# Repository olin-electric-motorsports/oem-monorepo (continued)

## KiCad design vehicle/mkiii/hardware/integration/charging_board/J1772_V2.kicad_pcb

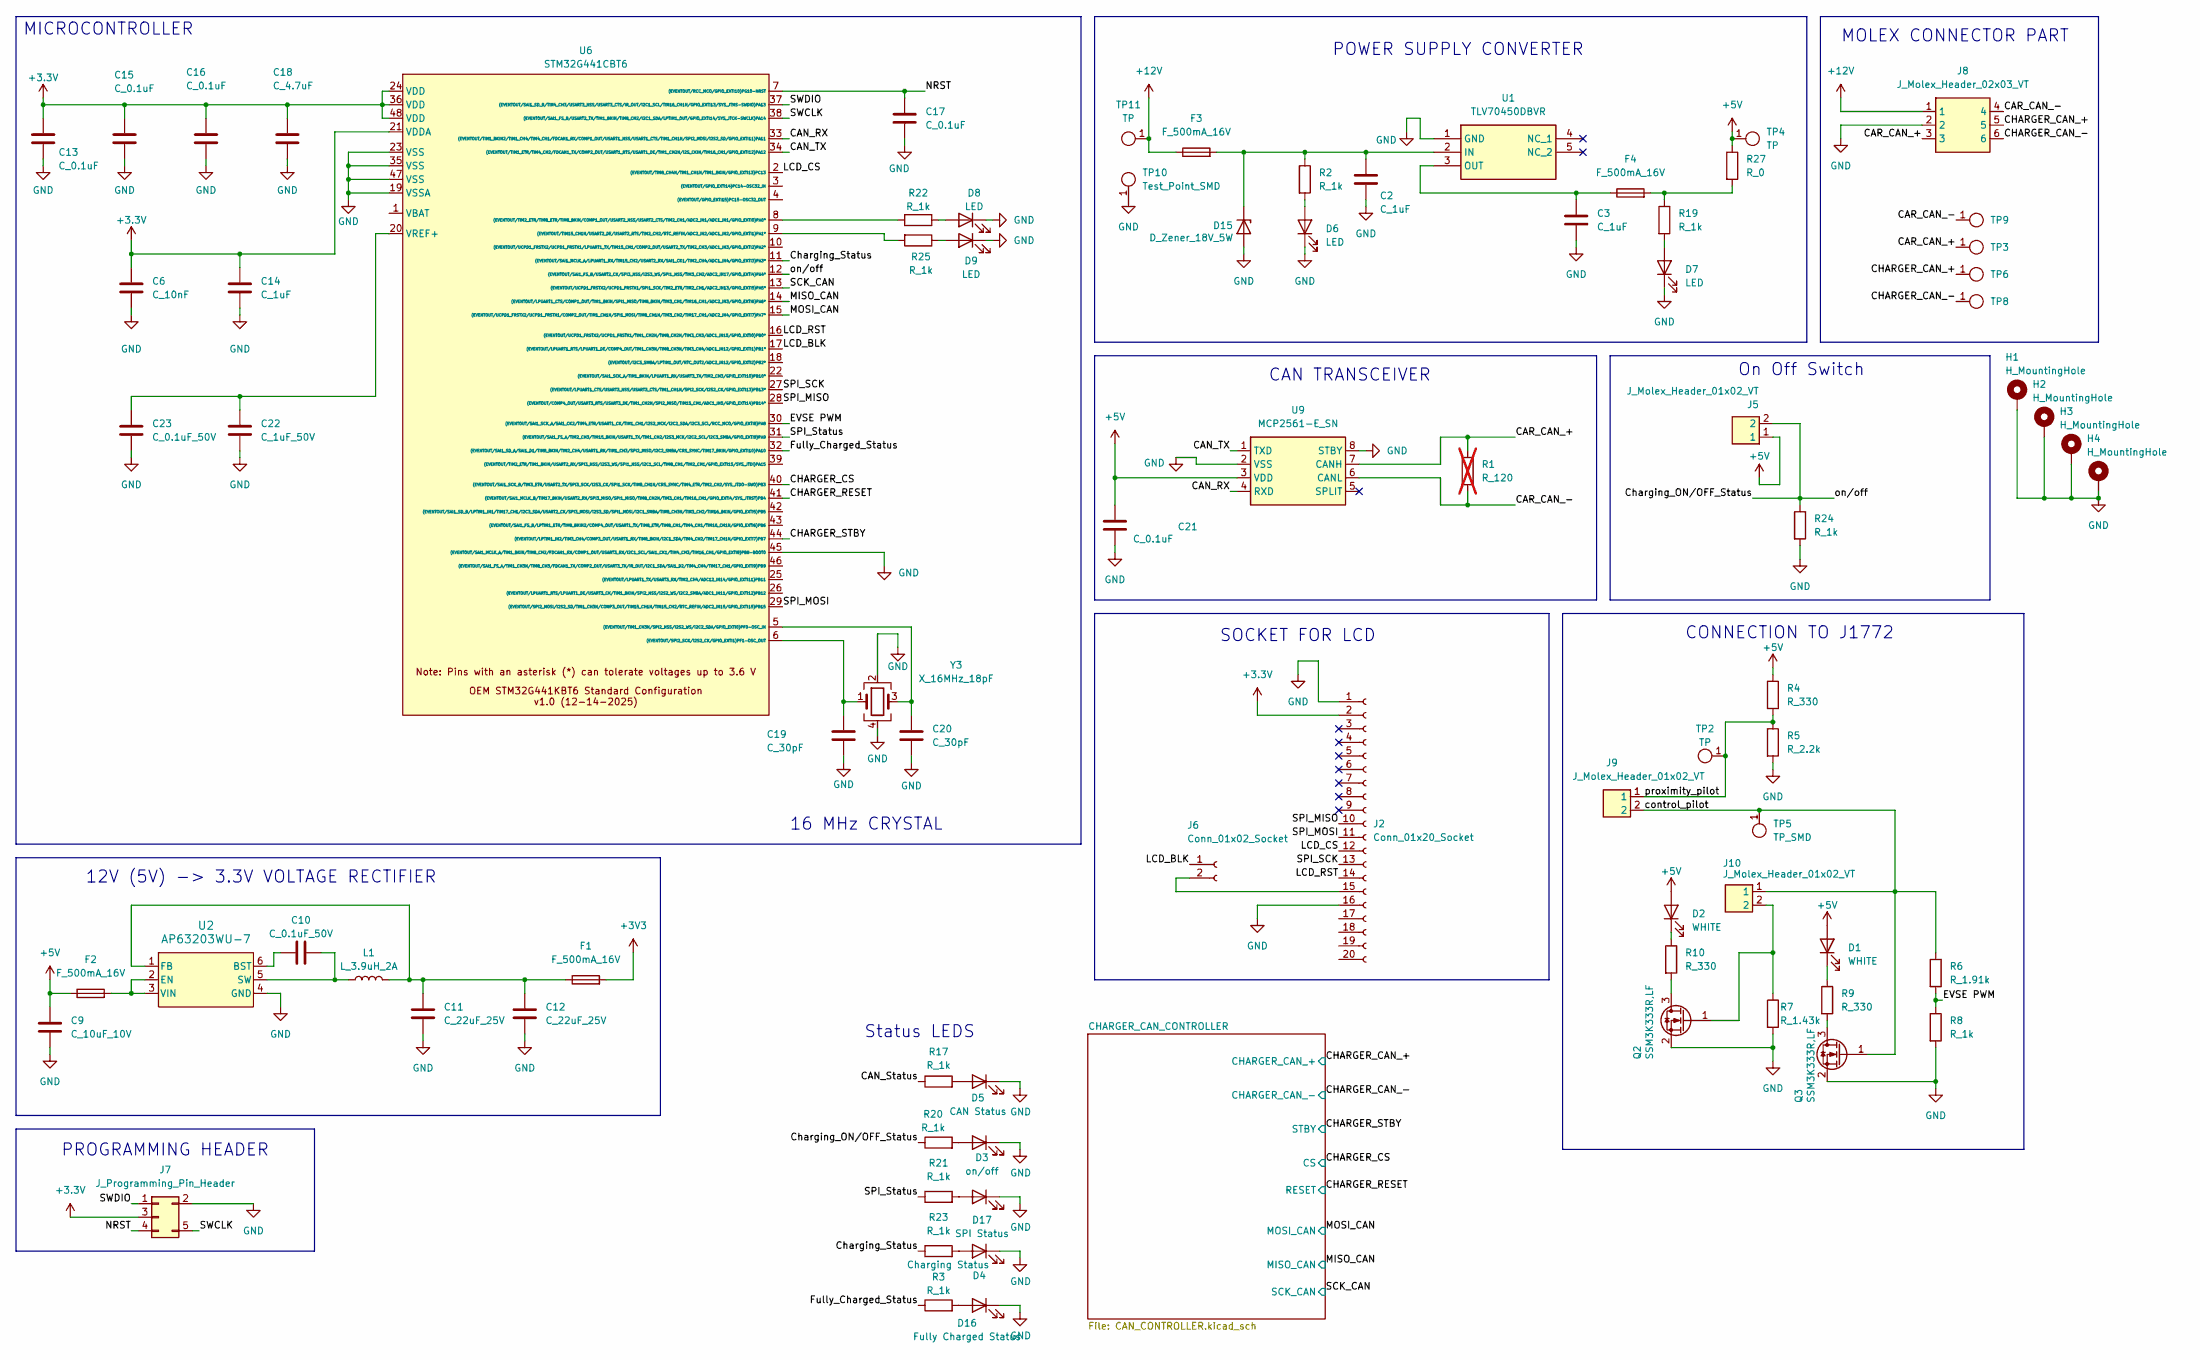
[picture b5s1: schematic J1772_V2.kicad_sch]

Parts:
C2, C14: C_1uF; C_0603_1608Metric; MPN UMK107BJ105KA-T
C3: C_1uF; C_0603_1608Metric; MPN CL10B105KA8NNNC
C6: C_10nF; C_0603_1608Metric; MPN CL10B103KB8NNNC
C9: C_10uF_10V; C_0603_1608Metric; MPN GRM188D71A106KA73D
C10, C23: C_0.1uF_50V; C_0603_1608Metric; MPN CL10B104KB8NNWC
C11, C12: C_22uF_25V; C_1206_3216Metric; MPN CL31A226KAHNNNE
C13, C15, C16, C17, C21: C_0.1uF; C_0603_1608Metric; MPN CL10B104KB8NNWC
C18: C_4.7uF; C_0603_1608Metric; MPN GRT188R61E475ME13D
C19, C20: C_30pF; C_0603_1608Metric; MPN CML0603C0G300JT50V
C22: C_1uF_50V; C_0603_1608Metric; MPN UMK107BJ105KA-T
D1, D2: WHITE; D_0805_2012Metric; MPN QBLP631-IW
D3: on/off; D_0805_2012Metric; MPN LTST-C171KRKT
D4: Charging Status; D_0805_2012Metric; MPN LTST-C171AKT
D5: CAN Status; D_0805_2012Metric; MPN LTST-C171TBKT
D6, D7, D8, D9: LED; D_0805_2012Metric; MPN QBLP631-IW
D15: D_Zener_18V_5W; D_Zener_18V_5W_DO214AA - DIOM5336X262N; MPN SMBJ5355B-TP
D16: Fully Charged Status; D_0805_2012Metric; MPN LTST-C170KGKT
D17: SPI Status; D_0805_2012Metric; MPN QBLP631-IW
F1, F2, F3, F4: F_500mA_16V; Fuse_1210_3225Metric; MPN 0ZCH0050FF2G
H1, H2, H3, H4: H_MountingHole
J2: Conn_01x20_Socket; PinSocket_1x20_P2.54mm_Vertical
J5, J9, J10: J_Molex_Header_01x02_VT; J_Molex_Header_01x02_VT - 43045-02YY_121314; MPN 43045-0212
J6: Conn_01x02_Socket; PinSocket_1x02_P2.54mm_Vertical
J7: J_Programming_Pin_Header; J_Programming_Pin_Header_Keyed
J8: J_Molex_Header_02x03_VT; J_Molex_Header_02x03_VT - 43045-06YY_121314; MPN 43045-0614
L1: L_3.9uH_2A; IND_BOURNS_SRR5018 (L_3.9uH_2A_55m_SMD); MPN SRR5018-3R9Y
Q2, Q3: SSM3K333R,LF; SOT-23-3
R1: R_120; R_0603_1608Metric; MPN RC0603FR-13120RL; not fitted
R2, R3, R8, R17, R19, R20, R21, R22, R23, R24, R25: R_1k; R_0603_1608Metric; MPN RMCF0603FT1K00 (or ERJ-3GEYJ102V)
R4, R9, R10: R_330; R_0603_1608Metric; MPN RMCF0603FT330R (or WR06X3300FTL)
R5: R_2.2k; R_0603_1608Metric; MPN WR06X222 JTL
R6: R_1.91k; R_0603_1608Metric; MPN RMCF0603FT1K91
R7: R_1.43k; R_0603_1608Metric; MPN RMCF0603FT1K43
R27: R_0; R_2512_6332Metric; MPN CR2512-J/-000ELF
TP2, TP4, TP11: TP; TP_Hook_SMD; MPN 5019
TP3, TP5, TP6, TP8, TP9: TP_SMD; TP_Hook_SMD; MPN 5019
TP10: Test_Point_SMD; TP_Hook_SMD; MPN 5019
U1: TLV70450DBVR; SOT-23-5; MPN TLV70450DBVR
U2: AP63203WU-7; SOT-23-6; MPN AP63203WU-7
U6: STM32G441CBT6; LQFP-48_7x7mm_P0.5mm; MPN STM32G441CBT6
U9: MCP2561-E_SN; SOIC-8_3.9x4.9mm_P1.27mm; MPN MCP2561-E/SN
Y3: X_16MHz_18pF; FA238160000MBC0 (X_16MHz_18pF_SMD - FA-238_16.0000MB-C0); MPN FA-238 16.0000MB-C0

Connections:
+5V: C9.1, C21.1, D1.2 (A), D2.2 (A), F2.1, J5.1, R4.1, R27.1, TP4.1, U9.3 (VDD); also elsewhere on the board
+12V: F3.1, J8.1, TP11.1
/CAN_RX: U6.33 ((EVENTOUT/TIM1_BKIN2/TIM1_CH4/TIM4_CH1/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), U9.4 (RXD)
/CAN_Status: R17.1
/CAN_TX: U6.34 ((EVENTOUT/TIM1_ETR/TIM4_CH2/FDCAN1_TX/C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), U9.1 (TXD)
/CAR_CAN_+: J8.3, R1.1, TP3.1, U9.7 (CANH)
/CAR_CAN_-: J8.4, R1.2, TP9.1, U9.6 (CANL)
/CHARGER_CAN_+: J8.5, TP6.1; also elsewhere on the board
/CHARGER_CAN_-: J8.6, TP8.1; also elsewhere on the board
/CHARGER_CS: U6.40 ((EVENTOUT/SAI1_SCK_B/TIM3_ETR/USART2_TX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); also elsewhere on the board
/CHARGER_RESET: U6.41 ((EVENTOUT/SAI1_MCLK_B/TIM17_BKIN/USART2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); also elsewhere on the board
/CHARGER_STBY: U6.44 ((EVENTOUT/LPTIM1_IN2/TIM3_CH4/COMP3_OUT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); also elsewhere on the board
/Charging_ON/OFF_Status: J5.2, R20.1, R24.1, U6.12 ((EVENTOUT/SAI1_FS_B/USART2_CK/SPI3_NSS/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)
/Charging_Status: R23.1, U6.11 ((EVENTOUT/SAI1_MCLK_A/LPUART1_RX/TIM15_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)
/EVSE PWM: R6.2, R8.1, U6.30 ((EVENTOUT/SAI1_SCK_A/SAI1_CK2/TIM4_ETR/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)
/Fully_Charged_Status: R3.1, U6.32 ((EVENTOUT/SAI1_SD_A/SAI1_D1/TIM8_BKIN/T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)
/LCD_BLK: J6.1, U6.17 ((EVENTOUT/LPUART1_RTS/LPUART1_DE/COMP4_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)
/LCD_CS: J2.12, U6.2 ((EVENTOUT/TIM8_CH4N/TIM1_CH1N/TIM1_BKIN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)
/LCD_RST: J2.14, U6.16 ((EVENTOUT/UCPD1_FRSTX2/UCPD1_FRSTX1/TIM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)
/MISO_CAN: U6.14 ((EVENTOUT/LPUART1_CTS/COMP1_OUT/TIM1_BK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); also elsewhere on the board
/MOSI_CAN: U6.15 ((EVENTOUT/UCPD1_FRSTX2/UCPD1_FRSTX1/COM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); also elsewhere on the board
/NRST: C17.1, J7.4, U6.7 ((EVENTOUT/RCC_MCO/GPIO_EXTI10)PG10-NRST)
/SCK_CAN: U6.13 ((EVENTOUT/UCPD1_FRSTX2/UCPD1_FRSTX1/SPI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); also elsewhere on the board
/SPI_MISO: J2.10, U6.28 ((EVENTOUT/COMP4_OUT/USART3_RTS/USART3_D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)
/SPI_MOSI: J2.11, U6.29 ((EVENTOUT/SPI2_MOSI/I2S2_SD/TIM1_CH3N/C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)
/SPI_SCK: J2.13, U6.27 ((EVENTOUT/LPUART1_CTS/USART3_NSS/USART3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)
/SPI_Status: R21.1, U6.31 ((EVENTOUT/SAI1_FS_A/TIM2_CH3/TIM15_BKIN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)
/SWCLK: J7.5, U6.38 ((EVENTOUT/SAI1_FS_B/USART2_TX/TIM1_BKIN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)
/SWDIO: J7.1, U6.37 ((EVENTOUT/SAI1_SD_B/TIM4_CH3/USART3_NSS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)
/control_pilot: J9.2, J10.1, Q3.1 (G), R6.1, TP5.1
/proximity_pilot: J9.1, R4.2, R5.1, TP2.1
GND: C2.2, C3.2, C6.2, C9.2, C11.2, C12.2, C13.2, C14.2, C15.2, C16.2, C17.2, C18.2, C19.2, C20.2, C21.2, C22.2, C23.2, D3.1 (K), D4.1 (K), D5.1 (K), D6.1 (K), D7.1 (K), D8.1 (K), D9.1 (K), D15.2 (A), D16.1 (K), D17.1 (K), H1.1, H2.1, H3.1, H4.1, J2.1, J2.16, J7.2, J8.2, Q2.2 (S), Q3.2 (S), R5.2, R7.2, R8.2, R24.2, TP10.1, U1.1 (GND), U2.4 (GND), U6.19 (VSSA), U6.23 (VSS), U6.35 (VSS), U6.45 ((EVENTOUT/SAI1_MCLK_A/TIM1_BKIN/TIM8_CH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), U6.47 (VSS), U9.2 (VSS), U9.8 (STBY), Y3.2, Y3.4; also elsewhere on the board
unnamed: D1.1 (K), R9.1
unnamed: D2.1 (K), R10.1
unnamed: D3.2 (A), R20.2
unnamed: D4.2 (A), R23.2
unnamed: D5.2 (A), R17.2
unnamed: D6.2 (A), R2.2
unnamed: D7.2 (A), R19.2
unnamed: D8.2 (A), R22.1
unnamed: D9.2 (A), R25.1
unnamed: C2.1, D15.1 (K), F3.2, R2.1, U1.2 (IN)
unnamed: D16.2 (A), R3.2
unnamed: D17.2 (A), R21.2
unnamed: F4.2, R19.1, R27.2
unnamed: J2.15, J6.2
unnamed: Q2.3 (D), R10.2
unnamed: J10.2, Q2.1 (G), R7.1
unnamed: Q3.3 (D), R9.2
unnamed: C3.1, F4.1, U1.3 (OUT)
unnamed: C10.1, U2.6 (BST)
unnamed: F2.2, U2.2 (EN), U2.3 (VIN)
unnamed: C11.1, C12.1, F1.1, L1.2, U2.1 (FB)
unnamed: C10.2, L1.1, U2.5 (SW)
unnamed: C19.1, U6.6 ((EVENTOUT/SPI2_SCK/I2S2_CK/GPIO_EXTI1)P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), Y3.1
unnamed: C20.1, U6.5 ((EVENTOUT/TIM1_CH3N/SPI2_NSS/I2S2_WS/I2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), Y3.3
unnamed: R22.2, U6.8 ((EVENTOUT/TIM2_ETR/TIM8_ETR/TIM8_BKIN/C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)
unnamed: R25.2, U6.9 ((EVENTOUT/TIM15_CH1N/USART2_DE/USART2_R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)
unnamed: C22.1, C23.1, U6.20 (VREF+)

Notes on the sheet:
MOLEX CONNECTOR PART
PROGRAMMING HEADER
SOCKET FOR LCD
12V (5V) -> 3.3V VOLTAGE RECTIFIER
On Off Switch
CAN TRANSCEIVER
MICROCONTROLLER
CONNECTION TO J1772
16 MHz CRYSTAL
POWER SUPPLY CONVERTER
Status LEDS

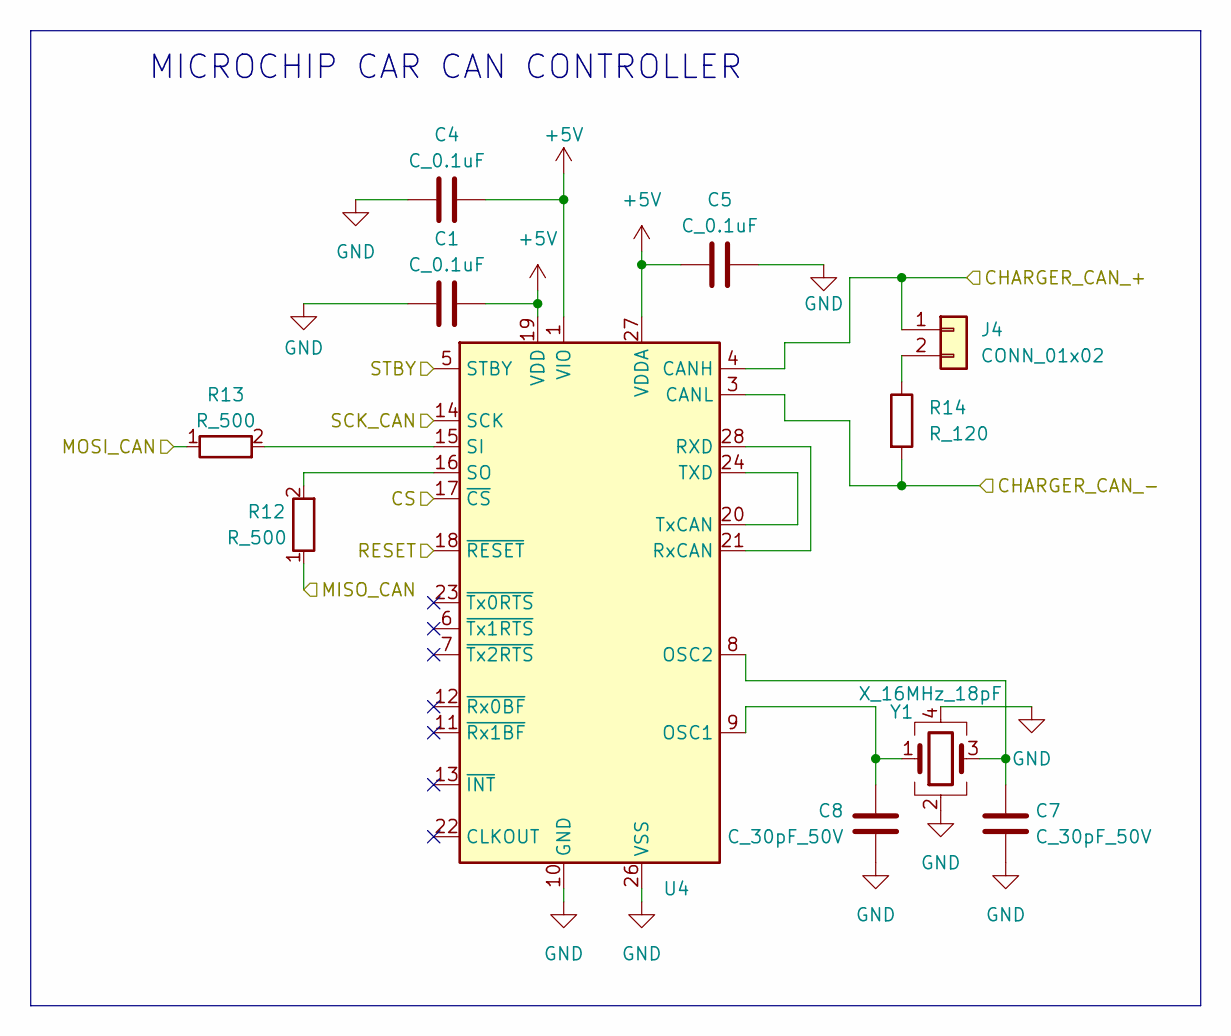
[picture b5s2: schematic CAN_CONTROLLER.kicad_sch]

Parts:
C1, C4, C5: C_0.1uF; C_0603_1608Metric; MPN CL10B104KB8NNWC
C7, C8: C_30pF_50V; C_0603_1608Metric; MPN CML0603C0G300JT50V
J4: CONN_01x02; PinHeader_1x02_P2.54mm_Vertical; MPN 732-5315-ND
R12, R13: R_500; R_0603_1608Metric; MPN 541-3305-1-ND
R14: R_120; R_0603_1608Metric; MPN 667-ERJ-6ENF1200V
U4: SSOP-28_5.3x10.2mm_P0.65mm; MPN MCP25625-E/SS-ND
Y1: X_16MHz_18pF; FA238160000MBC0 (X_16MHz_18pF_SMD - FA-238_16.0000MB-C0); MPN FA-238 16.0000MB-C0

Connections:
+5V: C1.1, C4.1, C5.2, U4.1 (VIO), U4.19 (VDD), U4.27 (VDDA); also elsewhere on the board
/CHARGER_CAN_+: J4.1, U4.4 (CANH); also elsewhere on the board
/CHARGER_CAN_-: R14.2, U4.3 (CANL); also elsewhere on the board
/CHARGER_CS: U4.17 (~CS); also elsewhere on the board
/CHARGER_RESET: U4.18 (~RESET); also elsewhere on the board
/CHARGER_STBY: U4.5 (STBY); also elsewhere on the board
/MISO_CAN: R12.1; also elsewhere on the board
/MOSI_CAN: R13.1; also elsewhere on the board
/SCK_CAN: U4.14 (SCK); also elsewhere on the board
GND: C1.2, C4.2, C5.1, C7.2, C8.2, U4.10 (GND), U4.26 (VSS), Y1.2, Y1.4; also elsewhere on the board
unnamed: J4.2, R14.1
unnamed: C8.1, U4.9 (OSC1), Y1.1
unnamed: C7.1, U4.8 (OSC2), Y1.3
unnamed: U4.21 (RxCAN), U4.28 (RXD)
unnamed: R13.2, U4.15 (SI)
unnamed: R12.2, U4.16 (SO)
unnamed: U4.20 (TxCAN), U4.24 (TXD)

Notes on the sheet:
MICROCHIP CAR CAN CONTROLLER

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
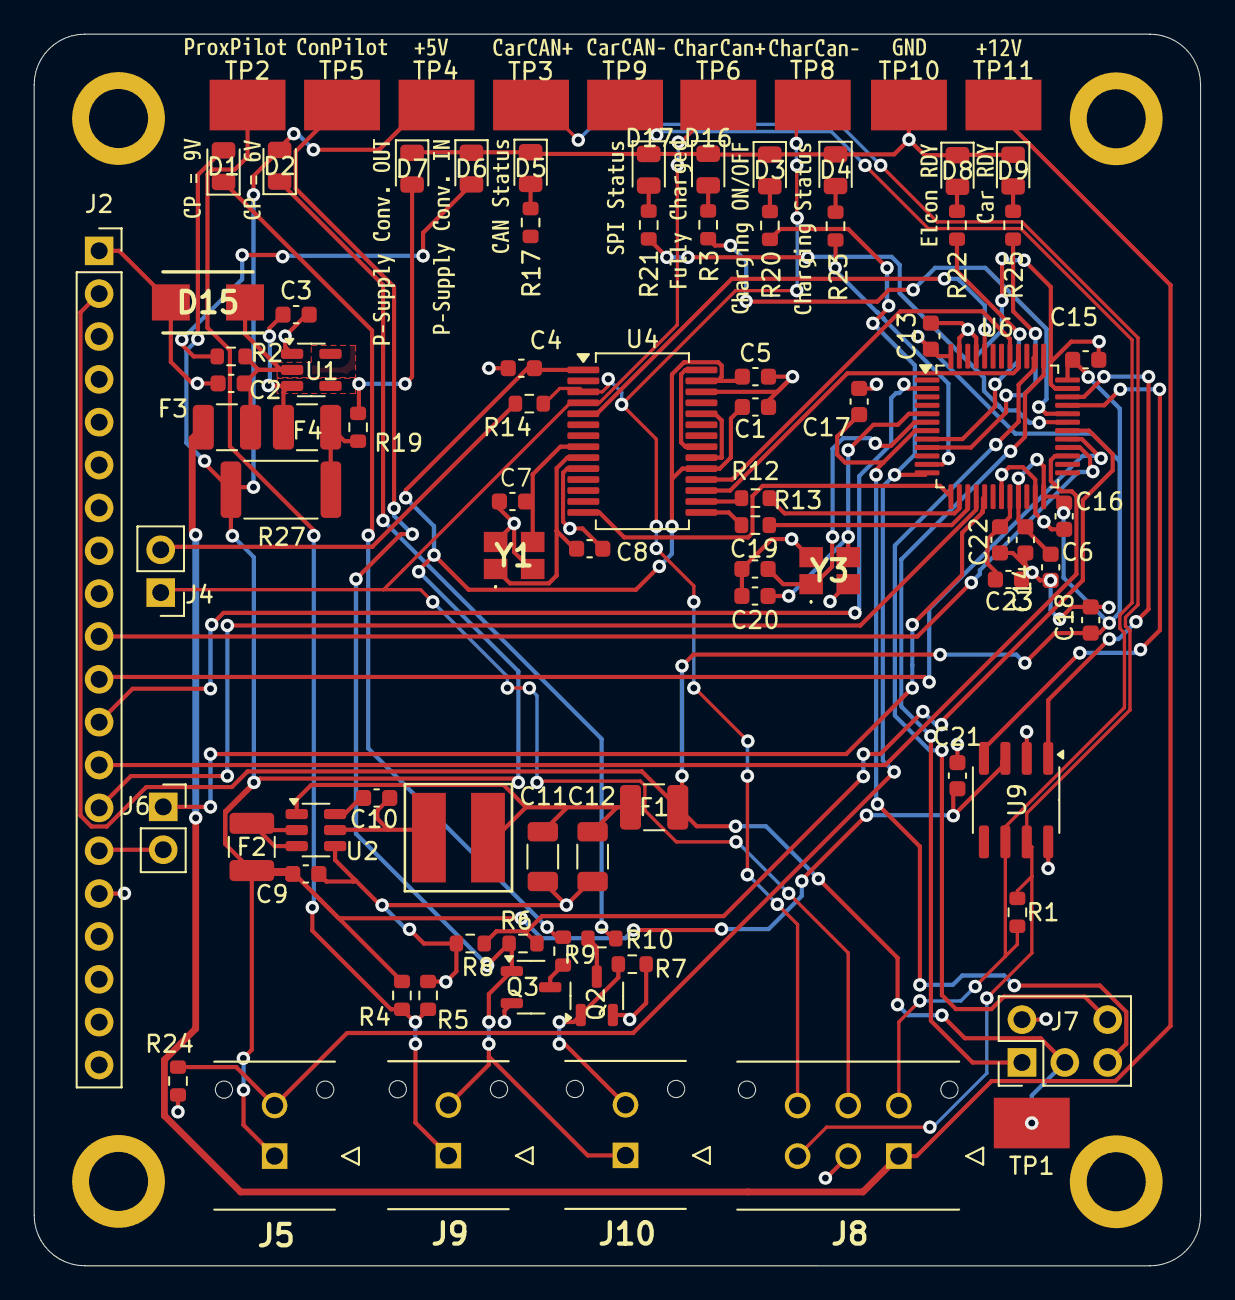
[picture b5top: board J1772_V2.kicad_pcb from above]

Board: 2 copper layers, 69.1 x 73.0 mm, 113 parts (0 on the bottom side), 66 nets.

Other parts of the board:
TP1: TP_SMD; TP_Hook_SMD
kibuzzard-697E8BFB: G***; kibuzzard-697E8BFB
kibuzzard-697E8C4A: G***; kibuzzard-697E8C4A
kibuzzard-697E8CB4: G***; kibuzzard-697E8CB4
kibuzzard-697E8D62: G***; kibuzzard-697E8D62
kibuzzard-697E8F0F: G***; kibuzzard-697E8F0F
kibuzzard-697E8F2E: G***; kibuzzard-697E8F2E
kibuzzard-697E8F4D: G***; kibuzzard-697E8F4D
kibuzzard-697E93AD: G***; kibuzzard-697E93AD
kibuzzard-697E93BE: G***; kibuzzard-697E93BE
kibuzzard-697E93CD: G***; kibuzzard-697E93CD
kibuzzard-697E924A: G***; kibuzzard-697E924A
kibuzzard-697E927F: G***; kibuzzard-697E927F
kibuzzard-697E935D: G***; kibuzzard-697E935D
kibuzzard-697E939F: G***; kibuzzard-697E939F
kibuzzard-697E940C: G***; kibuzzard-697E940C
kibuzzard-697E942B: G***; kibuzzard-697E942B
kibuzzard-697E9252: G***; kibuzzard-697E9252
kibuzzard-697E9291: G***; kibuzzard-697E9291
kibuzzard-697E9365: G***; kibuzzard-697E9365
kibuzzard-697E9418: G***; kibuzzard-697E9418

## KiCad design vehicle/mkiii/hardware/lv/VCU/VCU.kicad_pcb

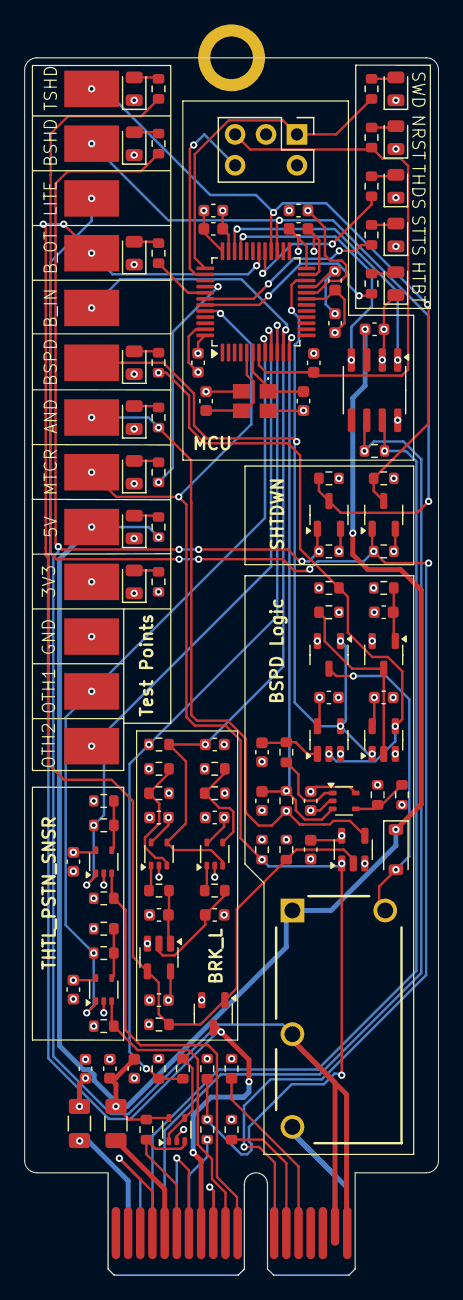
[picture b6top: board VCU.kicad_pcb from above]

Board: 4 copper layers, 34.0 x 100.0 mm, 128 parts (0 on the bottom side), 69 nets.

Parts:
C1, C3, C5, C7, C9, C14, C15, C17, C19, C20, C21, C23, C24, C27, C28, C29: C_0.1uF; C_0603_1608Metric
C2: C_10nF; C_0603_1608Metric
C4, C18: C_1uF; C_0603_1608Metric
C6: C_4.7uF; C_0603_1608Metric
C8, C10: C_30pF; C_0603_1608Metric
C11, C26: C_0.1uF_16V; C_0603_1608Metric
C12, C13, C16: C_10uF_10V; C_0603_1608Metric
C22: C_0.22uF_50V; C_0603_1608Metric
C25: C_1uF_25V; C_0603_1608Metric
D1: MOTOR_ON; D_0805_2012Metric
D2: BRAKES; D_0805_2012Metric
D3: BSPD_TRIP; D_0805_2012Metric
D4: HEARTBEAT; D_0805_2012Metric
D5: THROTTLE_DISABLE; D_0805_2012Metric
D6: 5V; D_0805_2012Metric
D7: 3V3; D_0805_2012Metric
D8: NRST; D_0805_2012Metric
D9: SWDIO; D_0805_2012Metric
D10: D_Amber_LED; D_0805_2012Metric
D11: D_36V_500mW; D_SOD-123
D12: BSPD_TRIP_LED; D_0805_2012Metric
D13, D14: D_Blue_LED; D_0805_2012Metric
F1, F2: F_500mA_8V; Fuse_1206_3216Metric
H1: H_MountingHole
J1: J_Programming_Pin_Header; J_Programming_Pin_Header_Keyed
J2: J_PCIe_x1; J_PCIe_x1_Key
K1: K_10A_5V; G5Q1A4DC5 (K_SPST-NO_10A_5V_TH - G5Q-1A4-DC5)
Q1, Q2, Q3, Q4, Q5: SSM3K333R,LF; SOT-23-3
R1, R2, R3, R4, R5, R7, R8, R9, R12: R_200; R_0603_1608Metric
R6, R20, R27, R33: R_1k; R_0603_1608Metric
R10: R_120; R_0603_1608Metric
R11, R13, R15, R17, R22, R23, R24, R26, R28, R32, R34, R35, R36, R39, R42: R_10k; R_0603_1608Metric
R14, R16: R_5.1k; R_0603_1608Metric
R18, R19, R25, R38, R41: R_100k; R_0603_1608Metric
R21: R_71.5k; R_0603_1608Metric
R29: R_75k; R_0603_1608Metric
R30: R_576; R_0603_1608Metric
R31: R_100; R_0603_1608Metric
R37, R40: R_3k; R_0603_1608Metric
R43, R46: R_1M; R_0603_1608Metric
R44, R47: R_0; R_0603_1608Metric
R45, R48: R_2.2k; R_0603_1608Metric
TP1: 5V; TP_Hook_SMD
TP2: 3V3; TP_Hook_SMD
TP3: GND; TP_Hook_SMD
TP4, TP5, TP6, TP7, TP8, TP9, TP10, TP11, TP12, TP13: TP_SMD; TP_Hook_SMD
U1: STM32G441CBT6; LQFP-48_7x7mm_P0.5mm
U2: MCP2561-E_SN; SOIC-8_3.9x4.9mm_P1.27mm
U3, U5, U8, U9, U11, U12: MCP6001T-I/LT; SOT-353_SC-70-5
U4: SN74LVC1G08DBVR; SOT-23-5
U6, U7: SN74LVC1G02DBVR; SOT-23-5
U10: SN74LVC1G32DBVR; SOT-23-5
Y1: X_16MHz_18pF; FA238160000MBC0 (X_16MHz_18pF_SMD - FA-238_16.0000MB-C0)

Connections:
+3V3: C1.1, C2.1, C3.1, C4.1, C5.1, C6.1, C7.1, C13.1, C15.2, C17.1, C20.1, C21.1, C23.1, C24.1, C27.1, C28.1, C29.1, F2.1, J1.3, R7.1, R11.1, R12.1, R18.1, R22.1, R25.1, R26.1, R30.1, R32.1, R39.1, R42.1, R43.1, R46.1, TP2.1, U1.20 (VREF+), U1.21 (VDDA), U1.24 (VDD), U1.36 (VDD), U1.48 (VDD), U4.5 (VCC), U5.5 (V+), U6.5 (VCC), U7.5 (VCC), U8.5 (V+), U9.5 (V+), U10.5 (VCC), U11.5 (V+), U12.5 (V+)
+5V: C11.1, C12.1, C14.1, D11.1 (K), F1.1, K1.1, R6.1, R13.1, TP1.1, U2.3 (VDD), U3.5 (V+)
/BSPD/BRAKELIGHT_LL: Q3.1 (G), R19.1, R36.1, TP8.1, U1.30 ((EVENTOUT/SAI1_SCK_A/SAI1_CK2/TIM4_ETR/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), U4.2, U10.4
/BSPD/BSPD_LL: Q2.1 (G), TP6.1, U1.22 ((EVENTOUT/SAI1_SCK_A/TIM1_BKIN/LPUART1_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), U6.4, U7.1
/BSPD/BSPD_RELAY_IN: J2.A17 (SHDN_IN/io_22), J2.A18 (SHDN_IN/io_24), K1.3
/BSPD/BSPD_RELAY_OUT: J2.B17 (SHDN_OUT/io_23), J2.B18 (SHDN_OUT/io_25), K1.2, Q4.1 (G), R37.1, R38.1
/BSPD/MOTOR_CURRENT_SENSE: R14.2, R15.1, R18.2, TP4.1, U1.44 ((EVENTOUT/LPTIM1_IN2/TIM3_CH4/COMP3_OUT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), U4.1
/BSPD/RC_TIMER_STATUS: C16.1, R21.2, U1.12 ((EVENTOUT/SAI1_FS_B/USART2_CK/SPI3_NSS/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), U5.3 (+)
/BrakeLight/BRAKELIGHT_CONN: J2.B8 (io_5), Q3.3 (D), TP9.1
/BrakeLight/BRAKE_PRESS_SENSE: R16.2, R17.1, R29.1, U1.10 ((EVENTOUT/UCPD1_FRSTX2/UCPD1_FRSTX1/LPU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)
/BrakeLight/BRAKE_PRESS_SENSE_FILTERED: C22.1, R29.2, TP7.1, U1.11 ((EVENTOUT/SAI1_MCLK_A/LPUART1_RX/TIM15_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), U8.4 (-), U9.3 (+)
/Microcontroller - STM32G441CBT6 (page 2)/5KW_LED: R1.1, U1.40 ((EVENTOUT/SAI1_SCK_B/TIM3_ETR/USART2_TX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)
/Microcontroller - STM32G441CBT6 (page 2)/BRAKE_LL_LED: R2.1, U1.41 ((EVENTOUT/SAI1_MCLK_B/TIM17_BKIN/USART2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)
/Microcontroller - STM32G441CBT6 (page 2)/BSPD_SHUTDOWN_SENSE: Q4.3 (D), R39.2, TP10.1, U1.27 ((EVENTOUT/LPUART1_CTS/USART3_NSS/USART3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)
/Microcontroller - STM32G441CBT6 (page 2)/BSPD_TRIP_LED: R3.1, U1.42 ((EVENTOUT/SAI1_SD_B/LPTIM1_IN1/TIM17_CH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)
/Microcontroller - STM32G441CBT6 (page 2)/CAN_+: J2.A4 (CAN+), R10.1, U2.7 (CANH)
/Microcontroller - STM32G441CBT6 (page 2)/CAN_-: J2.A5 (CAN-), R10.2, U2.6 (CANL)
/Microcontroller - STM32G441CBT6 (page 2)/CAN_RX: U1.33 ((EVENTOUT/TIM1_BKIN2/TIM1_CH4/TIM4_CH1/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), U2.4 (RXD)
/Microcontroller - STM32G441CBT6 (page 2)/CAN_TX: U1.34 ((EVENTOUT/TIM1_ETR/TIM4_CH2/FDCAN1_TX/C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), U2.1 (TXD)
/Microcontroller - STM32G441CBT6 (page 2)/HEARTBEAT_LED: R4.1, U1.43 ((EVENTOUT/SAI1_FS_B/LPTIM1_ETR/TIM8_BKI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)
/Microcontroller - STM32G441CBT6 (page 2)/NRST: C9.1, J1.4, R8.1, U1.7 ((EVENTOUT/RCC_MCO/GPIO_EXTI10)PG10-NRST)
/Microcontroller - STM32G441CBT6 (page 2)/OUTPUT_THROTTLE_1: R44.1, TP12.1, U1.8 ((EVENTOUT/TIM2_ETR/TIM8_ETR/TIM8_BKIN/C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), U11.1
/Microcontroller - STM32G441CBT6 (page 2)/OUTPUT_THROTTLE_2: R47.1, TP13.1, U1.9 ((EVENTOUT/TIM15_CH1N/USART2_DE/USART2_R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), U12.1
/Microcontroller - STM32G441CBT6 (page 2)/SS_INERTIA_OUTPUT: Q5.3 (D), R42.2, TP11.1, U1.28 ((EVENTOUT/COMP4_OUT/USART3_RTS/USART3_D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)
/Microcontroller - STM32G441CBT6 (page 2)/SWCLK: J1.5, U1.38 ((EVENTOUT/SAI1_FS_B/USART2_TX/TIM1_BKIN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)
/Microcontroller - STM32G441CBT6 (page 2)/SWDIO: J1.1, R9.1, U1.37 ((EVENTOUT/SAI1_SD_B/TIM4_CH3/USART3_NSS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)
/Microcontroller - STM32G441CBT6 (page 2)/THROTTLE_DISABLE: R5.1, U1.29 ((EVENTOUT/SPI2_MOSI/I2S2_SD/TIM1_CH3N/C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)
/PCIe x1 Connector/INPUT_THROTTLE_1: J2.B10 (io_9), R43.2, U11.3 (+)
/PCIe x1 Connector/INPUT_THROTTLE_2: J2.B11 (io_11), R46.2, U12.3 (+)
/PCIe x1 Connector/SS_INERTIA_SWITCH: J2.B12 (io_13), Q5.1 (G), R40.1, R41.1
/PCIe x1 Connector/THROTTLE_1+: J2.B13 (io_15), R11.2
/PCIe x1 Connector/THROTTLE_2+: J2.B14 (io_17), R12.2
GND: C1.2, C2.2, C3.2, C4.2, C5.2, C6.2, C7.2, C8.2, C9.2, C10.2, C11.2, C12.2, C13.2, C14.2, C15.1, C16.2, C17.2, C18.2, C19.1, C20.2, C21.2, C22.2, C23.2, C24.2, C25.2, C26.2, C27.2, C28.2, C29.2, D1.1 (K), D2.1 (K), D3.1 (K), D4.1 (K), D5.1 (K), D6.1 (K), D7.1 (K), D8.1 (K), D9.1 (K), D10.1 (K), D12.1 (K), D13.1 (K), D14.1 (K), H1.1, J1.2, J2.A3 (GND), J2.A6 (io_0), J2.A8 (io_4), J2.A9 (io_6), J2.A10 (io_8), J2.A11 (io_10), J2.A12 (io_12), J2.A13 (io_14), J2.A14 (io_16), J2.B4 (GND), J2.B7 (io_3), J2.B9 (io_7), Q1.2 (S), Q2.2 (S), Q3.2 (S), Q4.2 (S), Q5.2 (S), R15.2, R17.2, R19.2, R23.2, R28.1, R31.2, R33.2, R36.2, R38.2, R41.2, R45.2, R48.2, TP3.1, U1.19 (VSSA), U1.23 (VSS), U1.35 (VSS), U1.47 (VSS), U2.2 (VSS), U2.8 (STBY), U3.2 (V-), U4.3 (GND), U5.2 (V-), U6.3 (GND), U7.3 (GND), U8.2 (V-), U9.2 (V-), U10.3 (GND), U11.2 (V-), U12.2 (V-), Y1.2, Y1.4
unnamed: C18.1, R24.2, U6.1
unnamed: C25.1, R34.2, U10.1
unnamed: C26.1, R35.2, U10.2
unnamed: D1.2 (A), R1.2
unnamed: D2.2 (A), R2.2
unnamed: D3.2 (A), R3.2
unnamed: D4.2 (A), R4.2
unnamed: D5.2 (A), R5.2
unnamed: D6.2 (A), R6.2
unnamed: D7.2 (A), R7.2
unnamed: D8.2 (A), R8.2
unnamed: D9.2 (A), R9.2
unnamed: D10.2 (A), R20.2
unnamed: D11.2 (A), K1.5, Q2.3 (D)
unnamed: D12.2 (A), R27.2
unnamed: D13.2 (A), R37.2
unnamed: D14.2 (A), R40.2
unnamed: F2.2, J2.A2 (3.3V)
unnamed: F1.2, J2.B5 (5V)
unnamed: J2.B6 (io_1), R13.2, U3.3 (+)
unnamed: J2.A7 (io_2), R14.1
unnamed: Q1.3 (D), R25.2, U7.2
unnamed: C19.2, Q1.1 (G), R26.2
unnamed: R20.1, R21.1, TP5.1, U4.4
unnamed: R24.1, U5.1
unnamed: R27.1, R28.2, U6.2, U7.4
unnamed: R34.1, U8.1
unnamed: R35.1, U9.1
unnamed: C8.1, U1.6 ((EVENTOUT/SPI2_SCK/I2S2_CK/GPIO_EXTI1)P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), Y1.1
unnamed: C10.1, U1.5 ((EVENTOUT/TIM1_CH3N/SPI2_NSS/I2S2_WS/I2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), Y1.3
unnamed: R16.1, U3.1, U3.4 (-)
unnamed: R22.2, R23.1, U5.4 (-)
unnamed: R32.2, R33.1, U8.3 (+)
unnamed: R30.2, R31.1, U9.4 (-)
unnamed: R44.2, R45.1, U11.4 (-)
unnamed: R47.2, R48.1, U12.4 (-)
